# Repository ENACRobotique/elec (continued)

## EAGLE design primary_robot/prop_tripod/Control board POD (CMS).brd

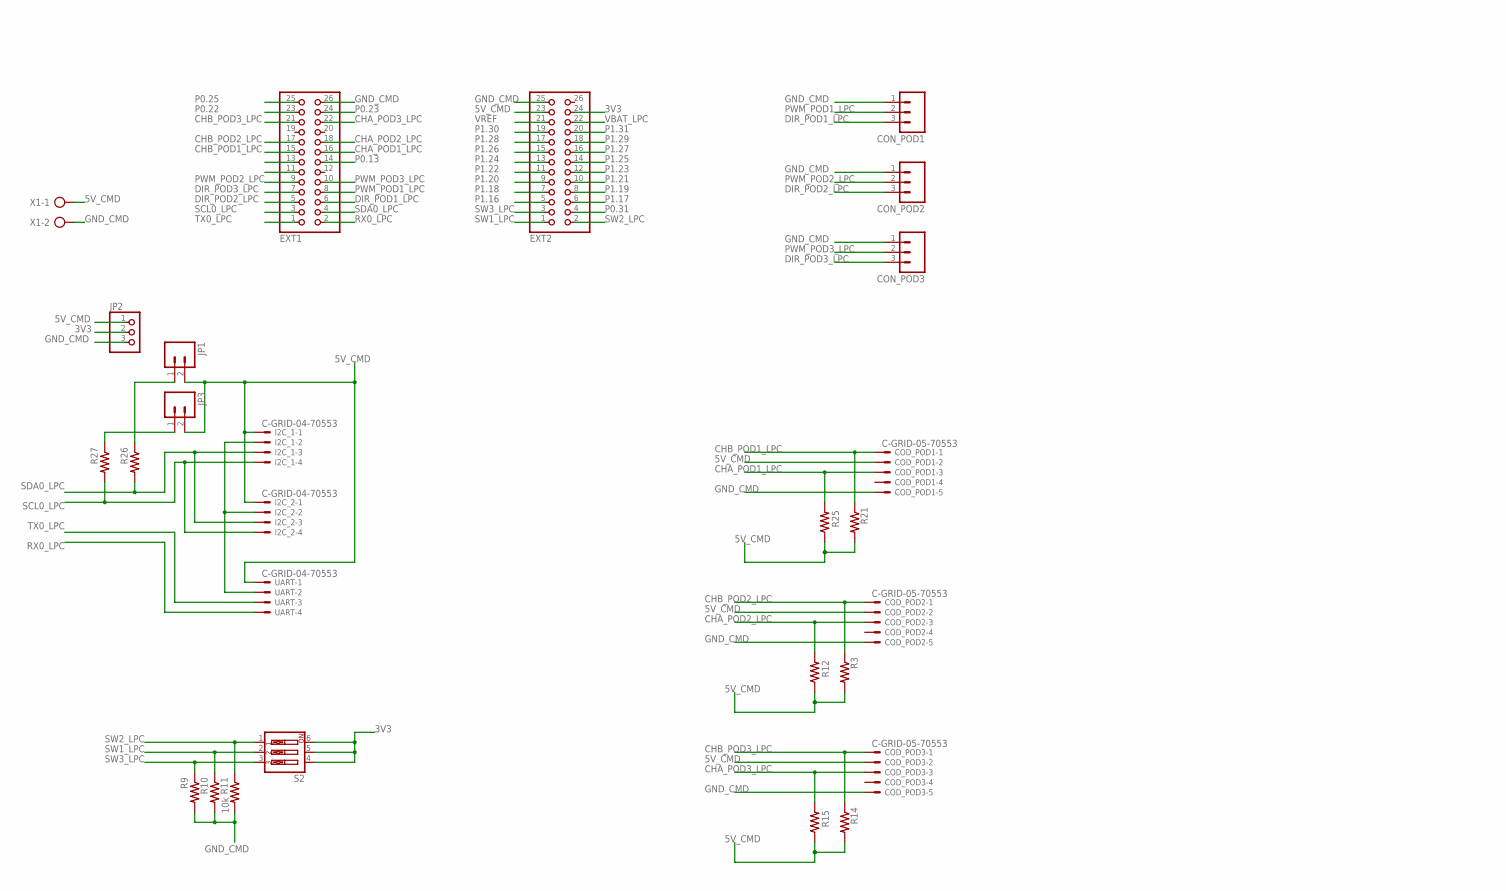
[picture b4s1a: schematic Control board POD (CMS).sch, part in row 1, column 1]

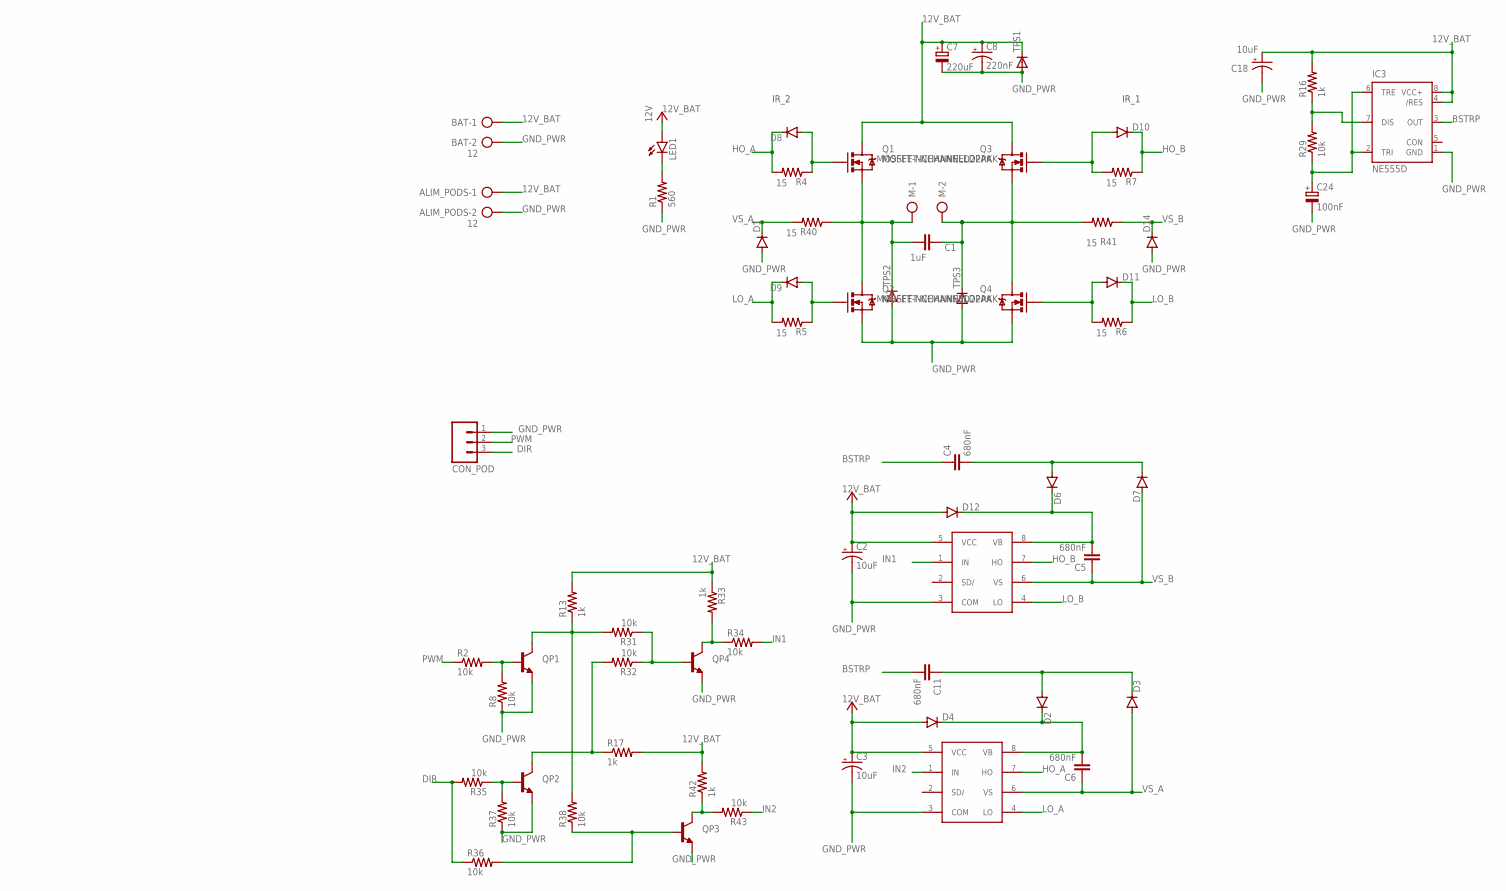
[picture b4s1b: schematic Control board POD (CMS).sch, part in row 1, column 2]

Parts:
ALIM_PODS: 12; AK500/2
BAT: 12; AK500/2
C1: 1uF; 0603-CAP
C2, C3, C18: 10uF; EIA3216
C4, C11: 680nF; 0805
C5, C6: 680nF; 1206
C7: 220uF; D/7343-31R
C8: 220nF; EIA3216
C24: 100nF; R/2012-12R
COD_POD1, COD_POD2, COD_POD3: C-GRID-05-70553; 70553-05
CON_POD, CON_POD1, CON_POD2, CON_POD3: M03PTH; 1X03
D1, D2, D3, D4, D6, D7, D8, D9, D10, D11, D12, D14: DIODESOD; SOD-323
EXT1, EXT2: PINHD-2X13; 2X13
I2C_1, I2C_2: C-GRID-04-70553; 70553-04
IC3: NE555D; SO08
IR2184SPBF1, IR2184SPBF2: IR2184SPBF; SO08
JP1, JP3: M02PTH; 1X02
JP2: PINHD-1X3; 1X03
LED1: LED-WHITE; LED-1206
M: AK500/2
Q1, Q2, Q3, Q4: MOSFET-NCHANNELD2PAK; D2PAK-3
QP1, QP2, QP3, QP4: TRANSISTOR_NPNSOT23-3; SOT23-3
R1: 560; 1206
R2, R8, R9, R10, R11, R29, R31, R32, R34, R35, R36, R37, R38, R43: 10k; 0603-RES
R3, R12, R14, R15, R21, R25: 3k3; 0603-RES
R4, R5, R6, R7: 15; 0805
R13, R16, R17, R33, R42: 1k; 0603-RES
R26, R27: 3.3k; 0603-RES
R40, R41: 15; 0603-RES
S2: SW_DIP-3; EDG-03
TPS1, TPS2, TPS3: DIODE-SMC; SMC
UART: C-GRID-04-70553; 70553-04
X1: AK500/2

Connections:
3V3: EXT2.24, JP2.2, S2.4, S2.5, S2.6
5V_CMD: COD_POD1.2, COD_POD2.2, COD_POD3.2, EXT2.23, I2C_1.1, I2C_2.1, JP1.2, JP2.1, JP3.2, R3.2, R12.1, R14.2, R15.1, R21.2, R25.1, UART.1, X1.1
12V_BAT: ALIM_PODS.1, BAT.1, C2.A (+), C3.A (+), C7.+, C8.A (+), C18.A (+), D4.A, D12.A, IC3.4 (/RES), IC3.8 (VCC+), IR2184SPBF1.5 (VCC), IR2184SPBF2.5 (VCC), LED1.A, Q1.4 (D), Q3.4 (D), R13.2, R16.2, R17.2, R33.1, R42.2, TPS1.C
BSTRP: C4.1, C11.2, IC3.3 (OUT)
CHA_POD1_LPC: COD_POD1.3, EXT1.16, R25.2
CHA_POD2_LPC: COD_POD2.3, EXT1.18, R12.2
CHA_POD3_LPC: COD_POD3.3, EXT1.22, R15.2
CHB_POD1_LPC: COD_POD1.1, EXT1.15, R21.1
CHB_POD2_LPC: COD_POD2.1, EXT1.17, R3.1
CHB_POD3_LPC: COD_POD3.1, EXT1.21, R14.1
DIR: CON_POD.3, R35.2, R36.1
DIR_POD1_LPC: CON_POD1.3, EXT1.6
DIR_POD2_LPC: CON_POD2.3, EXT1.5
DIR_POD3_LPC: CON_POD3.3, EXT1.7
GATE_Q3: D9.A, Q2.1 (G), R5.1
GATE_Q4: D10.A, Q3.1 (G), R7.2
GND_CMD: COD_POD1.5, COD_POD2.5, COD_POD3.5, CON_POD1.1, CON_POD2.1, CON_POD3.1, EXT1.26, EXT2.25, I2C_1.2, I2C_2.2, JP2.3, R9.2, R10.2, R11.2, UART.2, X1.2
GND_PWR: ALIM_PODS.2, BAT.2, C2.C (-), C3.C (-), C7.-, C8.C (-), C18.C (-), C24.-, CON_POD.1, D1.A, D14.A, IC3.1 (GND), IR2184SPBF1.3 (COM), IR2184SPBF2.3 (COM), Q2.3 (S), Q4.3 (S), QP1.2 (E), QP2.2 (E), QP3.2 (E), QP4.2 (E), R1.1, R8.1, R37.1, TPS1.A, TPS2.A, TPS3.A
HO_A: D8.C, IR2184SPBF2.7 (HO), R4.2
HO_B: D10.C, IR2184SPBF1.7 (HO), R7.1
IN1: IR2184SPBF1.1 (IN), R34.2
IN2: IR2184SPBF2.1 (IN), R43.1
LO_A: D9.C, IR2184SPBF2.4 (LO), R5.2
LO_B: D11.C, IR2184SPBF1.4 (LO), R6.1
unnamed: C11.1, D2.A, D3.C
unnamed: D8.A, Q1.1 (G), R4.1
unnamed: C1.2, M.2, Q3.3 (S), Q4.4 (D), R41.2, TPS3.C
unnamed: C6.2, D2.C, D4.C, IR2184SPBF2.8 (VB)
unnamed: C4.2, D6.A, D7.C
unnamed: C5.2, D6.C, D12.C, IR2184SPBF1.8 (VB)
unnamed: LED1.C, R1.2
unnamed: C1.1, M.1, Q1.3 (S), Q2.4 (D), R40.1, TPS2.C
unnamed: D11.A, Q4.1 (G), R6.2
unnamed: IC3.7 (DIS), R16.1, R29.2
unnamed: C24.+, IC3.2 (TRI), IC3.6 (TRE), R29.1
unnamed: JP1.1, R26.1
unnamed: QP1.1 (B), R2.2, R8.2
unnamed: JP3.1, R27.1
unnamed: QP2.1 (B), R35.1, R37.2
unnamed: QP3.1 (B), R36.2, R38.1
unnamed: QP1.3 (C), R13.1, R31.2, R38.2
unnamed: QP4.1 (B), R31.1, R32.1
unnamed: QP2.3 (C), R17.1, R32.2
unnamed: QP4.3 (C), R33.2, R34.1
unnamed: QP3.3 (C), R42.1, R43.2
P0.13: EXT1.14
P0.22: EXT1.23
P0.23: EXT1.24
P0.25: EXT1.25
P0.31: EXT2.4
P1.16: EXT2.5
P1.17: EXT2.6
P1.18: EXT2.7
P1.19: EXT2.8
P1.20: EXT2.9
P1.21: EXT2.10
P1.22: EXT2.11
P1.23: EXT2.12
P1.24: EXT2.13
P1.25: EXT2.14
P1.26: EXT2.15
P1.27: EXT2.16
P1.28: EXT2.17
P1.29: EXT2.18
P1.30: EXT2.19
P1.31: EXT2.20
PWM: CON_POD.2, R2.1
PWM_POD1_LPC: CON_POD1.2, EXT1.8
PWM_POD2_LPC: CON_POD2.2, EXT1.9
PWM_POD3_LPC: CON_POD3.2, EXT1.10
RX0_LPC: EXT1.2, UART.4
SCL0_LPC: EXT1.3, I2C_1.4, I2C_2.4, R27.2
SD2_POD1_LPC: EXT1.11
SD2_POD3_LPC: EXT1.13
SDA0_LPC: EXT1.4, I2C_1.3, I2C_2.3, R26.2
SW1_LPC: EXT2.1, R10.1, S2.2
SW2_LPC: EXT2.2, R11.1, S2.1
SW3_LPC: EXT2.3, R9.1, S2.3
TX0_LPC: EXT1.1, UART.3
VBAT_LPC: EXT2.22
VREF: EXT2.21
VS_A: C6.1, D1.C, D3.A, IR2184SPBF2.6 (VS), R40.2
VS_B: C5.1, D7.A, D14.C, IR2184SPBF1.6 (VS), R41.1

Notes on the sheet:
IR_2
IR_1

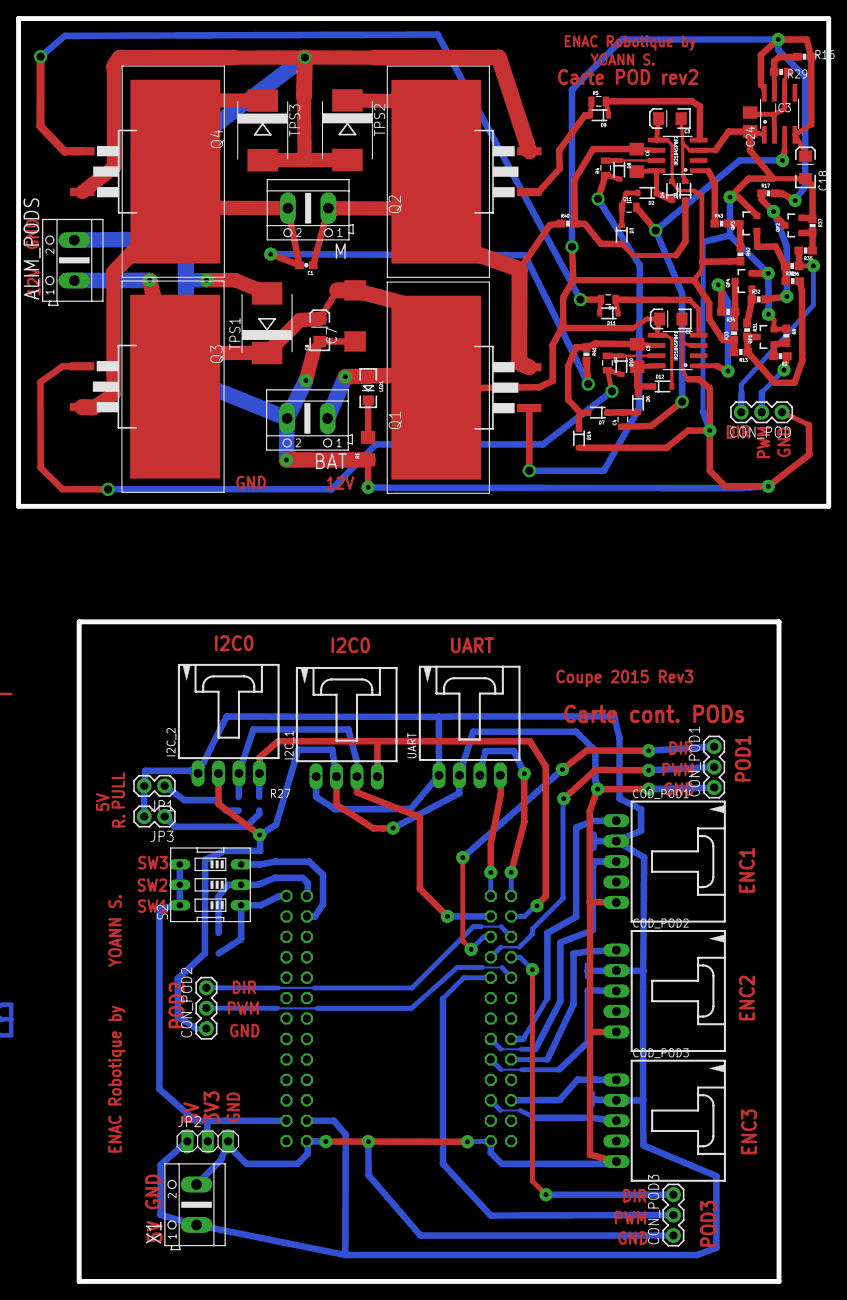
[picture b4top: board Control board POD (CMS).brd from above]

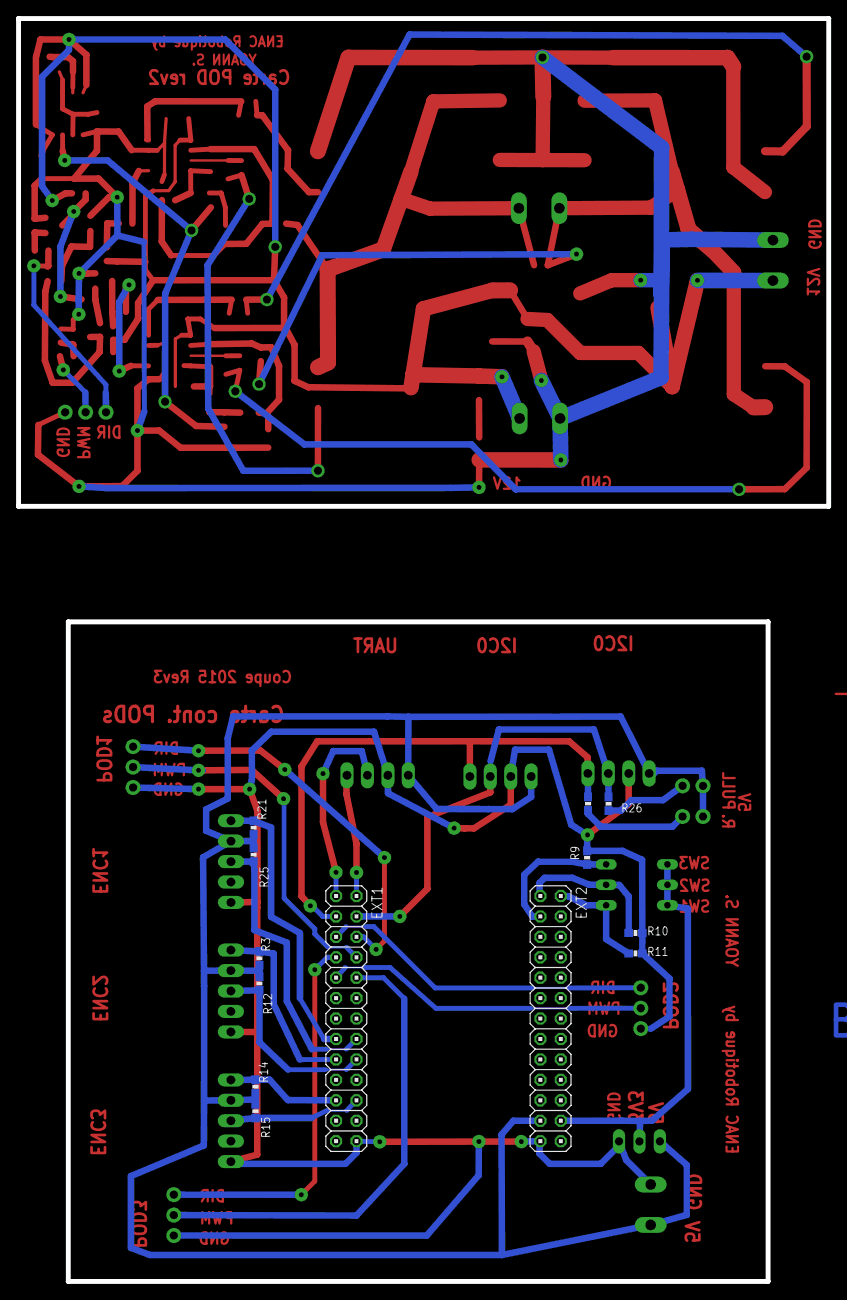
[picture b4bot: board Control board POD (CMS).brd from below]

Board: 2 copper layers, 100.7 x 157.0 mm, 92 parts (13 on the bottom side), 58 nets.

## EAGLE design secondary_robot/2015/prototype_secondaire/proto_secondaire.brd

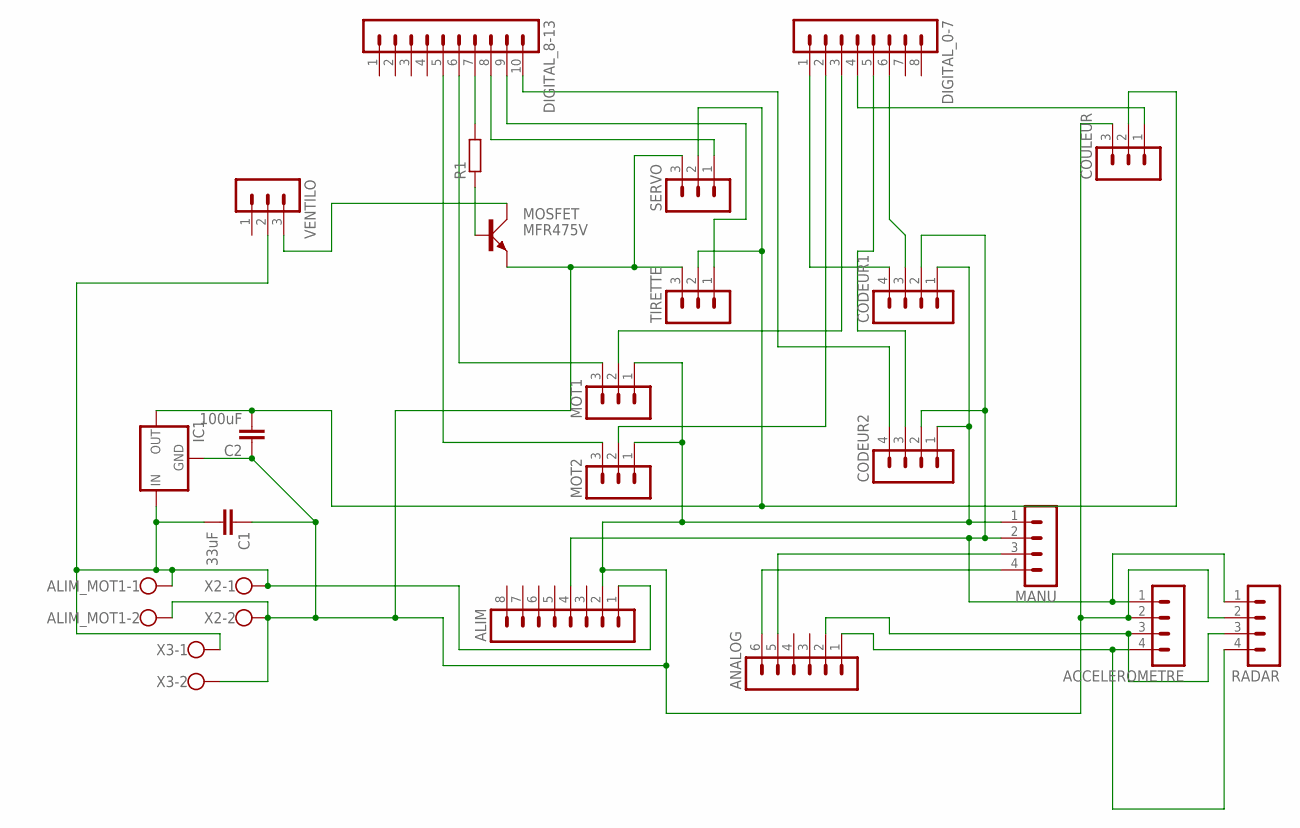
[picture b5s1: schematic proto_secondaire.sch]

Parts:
ACCELEROMETRE: MA04-1
ALIM: MA08-1
ALIM_MOT1: W237-102
ANALOG: MA06-1
C1: 33uF; C5B5
C2: 100uF; C5B5
CODEUR1, CODEUR2: MA04-1
COULEUR: MA03-1
DIGITAL_0-7: MA08-1
DIGITAL_8-13: MA10-1
IC1: 78XXS
MANU: MA04-1
MOSFET: MFR475V; TO220AV
MOT1, MOT2: MA03-1
R1: R-EU_0204/5; 0204/5
RADAR: MA04-1
SERVO: MA03-1
TIRETTE: MA03-1
VENTILO: MA03-1
X2, X3: W237-102

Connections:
CODEUR2_ETAT: CODEUR2.3, DIGITAL_0-7.5
unnamed: CODEUR1.4, DIGITAL_0-7.1
unnamed: ANALOG.5, MANU.3
unnamed: CODEUR2.4, DIGITAL_8-13.10
unnamed: CODEUR1.3, DIGITAL_0-7.6
unnamed: DIGITAL_0-7.2, MOT2.2
unnamed: DIGITAL_8-13.5, MOT2.3
unnamed: DIGITAL_0-7.3, MOT1.2
unnamed: DIGITAL_8-13.6, MOT1.3
unnamed: MOSFET.B, R1.1
unnamed: DIGITAL_8-13.7, R1.2
unnamed: ANALOG.6, MANU.4
unnamed: ALIM.1, ALIM_MOT1.1, C1.2, IC1.IN, VENTILO.2, X2.1, X3.1
unnamed: MOSFET.C, VENTILO.3
unnamed: COULEUR.1, DIGITAL_0-7.4
unnamed: DIGITAL_8-13.8, SERVO.1
unnamed: DIGITAL_8-13.9, TIRETTE.1
unnamed: C2.2, COULEUR.2, IC1.OUT, SERVO.2, TIRETTE.2
unnamed: ACCELEROMETRE.2, ALIM.2, ALIM_MOT1.2, C1.1, C2.1, CODEUR1.1, CODEUR2.1, COULEUR.3, IC1.GND, MANU.1, MOSFET.E, MOT1.1, MOT2.1, RADAR.2, SERVO.3, TIRETTE.3, X2.2, X3.2
unnamed: ACCELEROMETRE.4, ANALOG.1, RADAR.4
unnamed: ACCELEROMETRE.3, ANALOG.2, RADAR.3
unnamed: ACCELEROMETRE.1, ALIM.4, CODEUR1.2, CODEUR2.2, MANU.2, RADAR.1

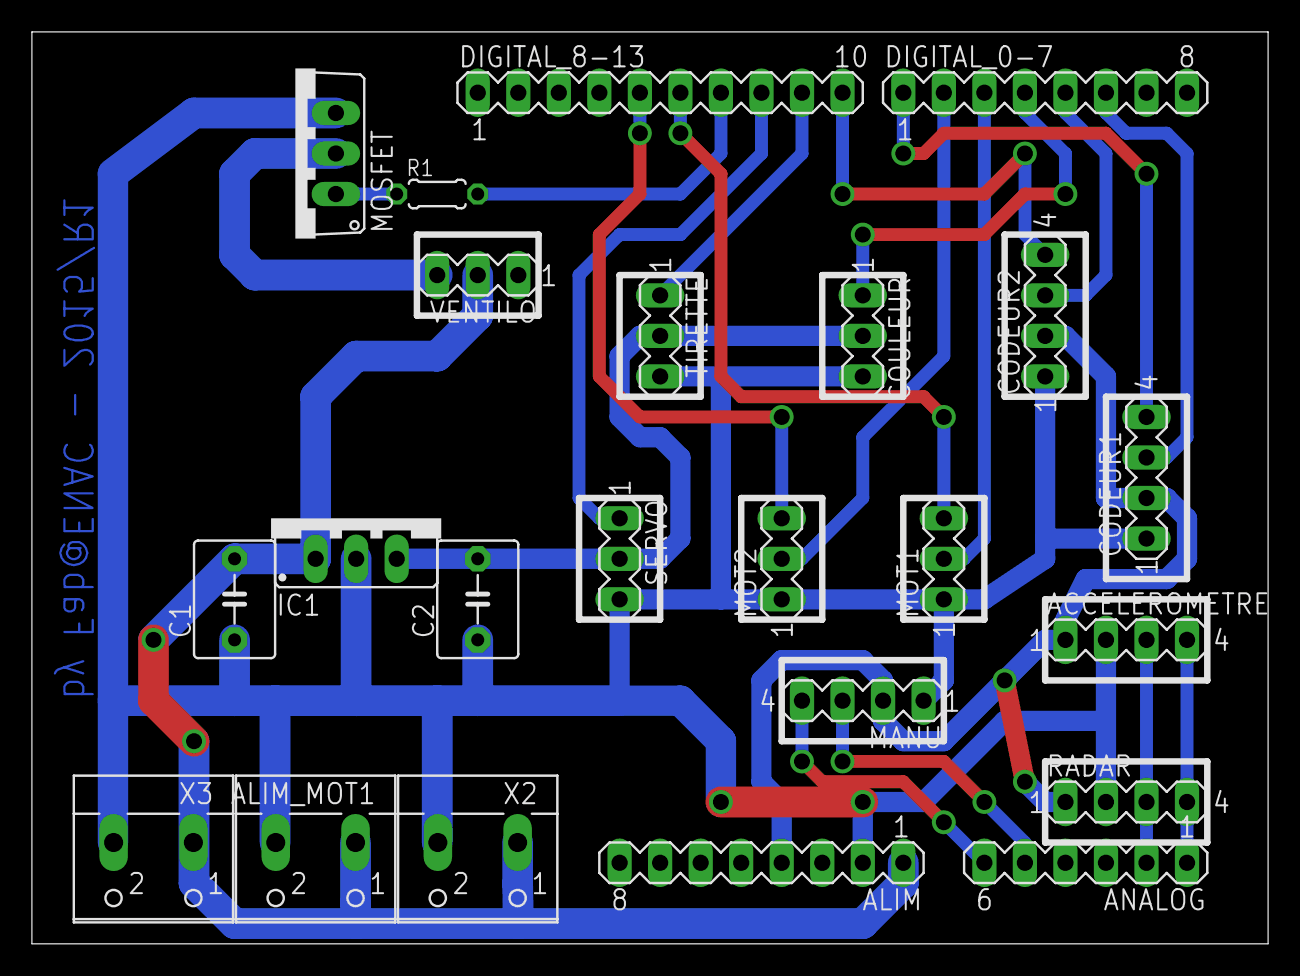
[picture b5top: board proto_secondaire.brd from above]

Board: 2 copper layers, 77.5 x 57.1 mm, 23 parts (0 on the bottom side), 22 nets.

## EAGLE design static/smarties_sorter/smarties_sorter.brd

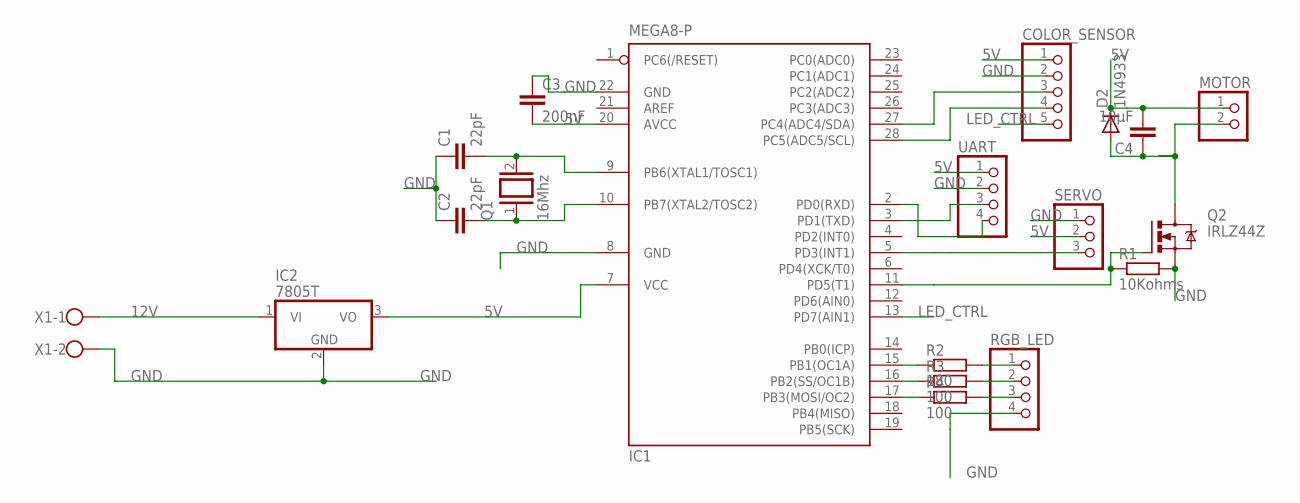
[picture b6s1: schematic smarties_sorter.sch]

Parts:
C1, C2: 22pF; C5B5
C3: 200nF; C5B3
C4: 10µF; C5B5
COLOR_SENSOR: PINHD-1X5; 1X05
D2: 1N4933; DO41-10
IC1: MEGA8-P; DIL28-3
IC2: 7805T; TO220H
MOTOR: PINHD-1X2; 1X02
Q1: 16Mhz; QS
Q2: IRLZ44Z; TO220BH
R1: 10Kohms; 0414/15
R2: 180; 0411/12
R3, R4: 100; 0411/12
RGB_LED: PINHD-1X4; 1X04
SERVO: PINHD-1X3; 1X03
UART: PINHD-1X4; 1X04
X1: W237-102

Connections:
5V: C3.2, C4.2, COLOR_SENSOR.1, D2.C, IC1.7 (VCC), IC1.20 (AVCC), IC2.3 (VO), MOTOR.1, SERVO.2, UART.1
12V: IC2.1 (VI), X1.1
B_LED: IC1.17 (PB3(MOSI/OC2)), R4.1
DRAIN: C4.1, D2.A, MOTOR.2, Q2.D
GND: C1.1, C2.1, C3.1, COLOR_SENSOR.2, IC1.8 (GND), IC1.22 (GND), IC2.2 (GND), Q2.S, R1.2, RGB_LED.4, SERVO.1, UART.2, X1.2
G_LED: IC1.16 (PB2(SS/OC1B)), R3.1
LED_CTRL: COLOR_SENSOR.5, IC1.13 (PD7(AIN1))
MOTOR_CMD: IC1.11 (PD5(T1)), Q2.G, R1.1
unnamed: C1.2, IC1.9 (PB6(XTAL1/TOSC1)), Q1.2
unnamed: C2.2, IC1.10 (PB7(XTAL2/TOSC2)), Q1.1
unnamed: R2.2, RGB_LED.1
unnamed: R3.2, RGB_LED.2
unnamed: R4.2, RGB_LED.3
RX: IC1.2 (PD0(RXD)), UART.4
R_LED: IC1.15 (PB1(OC1A)), R2.1
SCL: COLOR_SENSOR.4, IC1.28 (PC5(ADC5/SCL))
SDA: COLOR_SENSOR.3, IC1.27 (PC4(ADC4/SDA))
SERVO_CMD: IC1.5 (PD3(INT1)), SERVO.3
TX: IC1.3 (PD1(TXD)), UART.3

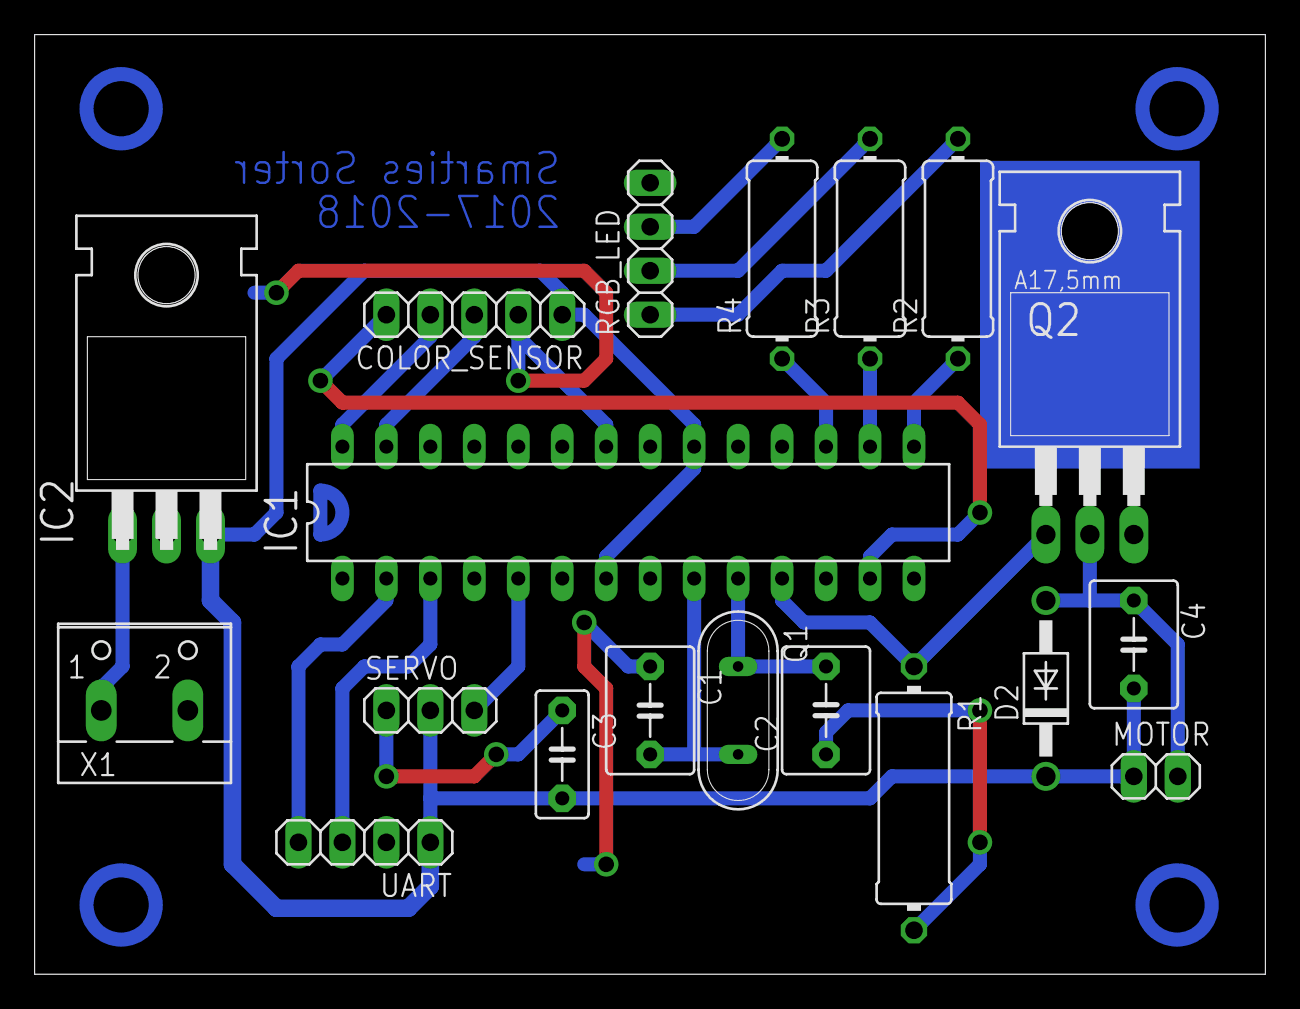
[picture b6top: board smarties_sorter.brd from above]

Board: 2 copper layers, 71.1 x 54.3 mm, 19 parts (0 on the bottom side), 19 nets.

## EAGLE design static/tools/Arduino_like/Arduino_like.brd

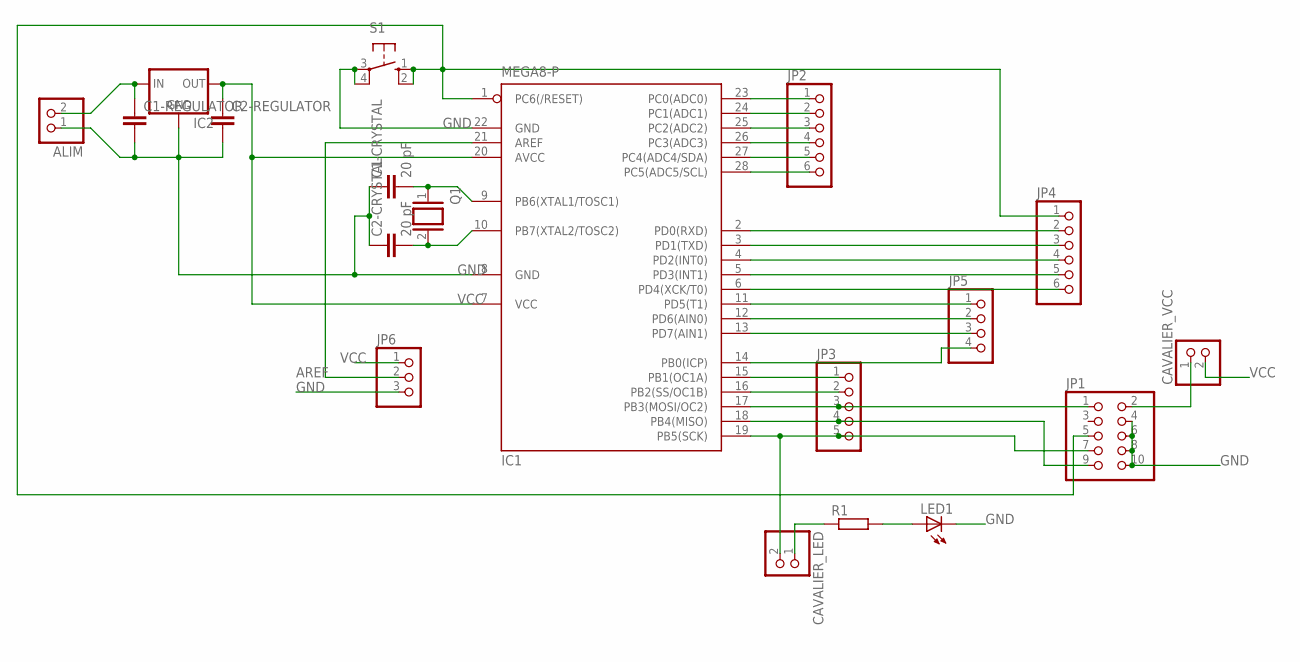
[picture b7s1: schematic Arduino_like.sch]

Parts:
ALIM: PINHD-1X2; 1X02
C1-CRYSTAL, C2-CRYSTAL: 20 pF; C5B5
C1-REGULATOR, C2-REGULATOR: C5/3.5; C5B3.5
CAVALIER_LED: PINHD-1X2; 1X02
CAVALIER_VCC: PINHD-1X2; 1X02
IC1: MEGA8-P; DIL28-3
IC2: 78XXS
JP1: PINHD-2X5; 2X05
JP2, JP4: PINHD-1X6; 1X06
JP3: PINHD-1X5; 1X05
JP5: PINHD-1X4; 1X04
JP6: PINHD-1X3; 1X03
LED1: LED3MM
Q1: XTAL/S; QS
R1: R-EU_0204/7; 0204/7
S1: 10-XX; B3F-10XX

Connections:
AREF: IC1.21 (AREF), JP6.2
GND: ALIM.1, C1-CRYSTAL.1, C1-REGULATOR.2, C2-CRYSTAL.1, C2-REGULATOR.2, IC1.8 (GND), IC1.22 (GND), IC2.GND, JP1.4, JP1.6, JP1.8, JP1.10, JP6.3, LED1.K (C), S1.3, S1.4 (P1)
unnamed: C1-CRYSTAL.2, IC1.9 (PB6(XTAL1/TOSC1)), Q1.1
unnamed: C2-CRYSTAL.2, IC1.10 (PB7(XTAL2/TOSC2)), Q1.2
unnamed: IC1.17 (PB3(MOSI/OC2)), JP1.1, JP3.3
unnamed: IC1.1 (PC6(/RESET)), JP1.5, JP4.1, S1.1 (S), S1.2 (S1)
unnamed: CAVALIER_LED.2, IC1.19 (PB5(SCK)), JP1.7, JP3.5
unnamed: ALIM.2, C1-REGULATOR.1, IC2.IN
unnamed: IC1.18 (PB4(MISO)), JP1.9, JP3.4
unnamed: IC1.23 (PC0(ADC0)), JP2.1
unnamed: IC1.24 (PC1(ADC1)), JP2.2
unnamed: IC1.25 (PC2(ADC2)), JP2.3
unnamed: IC1.26 (PC3(ADC3)), JP2.4
unnamed: IC1.27 (PC4(ADC4/SDA)), JP2.5
unnamed: IC1.28 (PC5(ADC5/SCL)), JP2.6
unnamed: IC1.2 (PD0(RXD)), JP4.2
unnamed: CAVALIER_VCC.1, JP1.2
unnamed: IC1.3 (PD1(TXD)), JP4.3
unnamed: IC1.4 (PD2(INT0)), JP4.4
unnamed: IC1.5 (PD3(INT1)), JP4.5
unnamed: IC1.6 (PD4(XCK/T0)), JP4.6
unnamed: IC1.11 (PD5(T1)), JP5.1
unnamed: IC1.12 (PD6(AIN0)), JP5.2
unnamed: IC1.13 (PD7(AIN1)), JP5.3
unnamed: IC1.14 (PB0(ICP)), JP5.4
unnamed: IC1.15 (PB1(OC1A)), JP3.1
unnamed: IC1.16 (PB2(SS/OC1B)), JP3.2
unnamed: CAVALIER_LED.1, R1.1
unnamed: LED1.A, R1.2
VCC: C2-REGULATOR.1, CAVALIER_VCC.2, IC1.7 (VCC), IC1.20 (AVCC), IC2.OUT, JP6.1

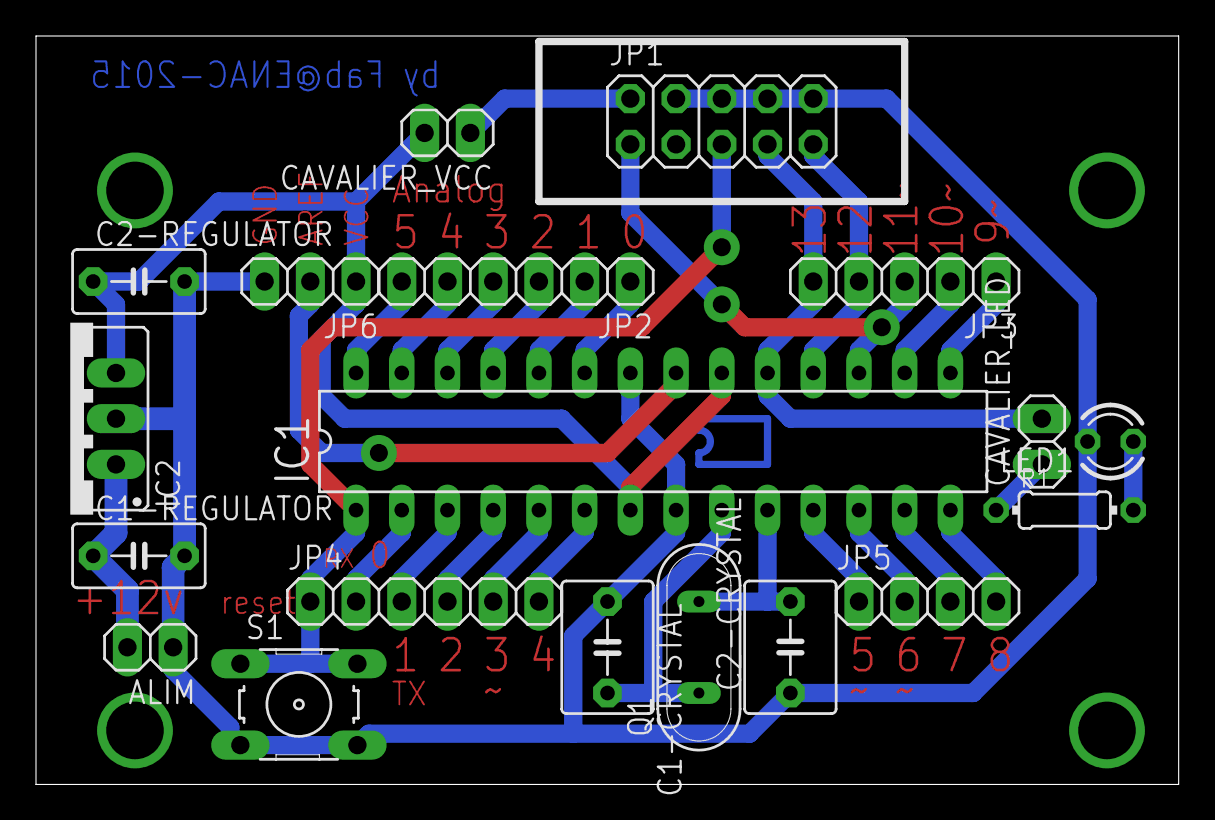
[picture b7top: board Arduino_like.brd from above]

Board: 2 copper layers, 63.5 x 41.6 mm, 19 parts (0 on the bottom side), 30 nets.
